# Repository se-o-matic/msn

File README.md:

# MSN

## MySensors Nodes
Hardware and software for MySensors.org IOT network.

The MSN PCB can be used for different node types. The minimal assembly consists of a Mega328P microcontroller (as seen on many Arduinos), a RFM69CW rf module with 868 or 433 MHz and some little stuff for reverse protection and battery monitoring.

With different assembly options, this PCB can be used for:
  * Temperature, humidity and pressure measurements (With BME280 assembled)
  * Sensor above with additional light level (with extra BH1750 on the proto field)
  * Cheap temperature measurement (With DS18B20 assembled on the small proto field)
  * IR-reader for digital Power meter (with external IR Head connected to UART)
  * Prototyping on Breadboards with soldered pin header

The PCB features also
  * ISP pins are connected to the pin header for flashing the bootloader
  * Arduino pro mini compatible pin header for connecting a UART-board
  * Optional LED for example for active transmission
  * Mounting holes for fitting in the “Strapubox 6090” case
  * A snap off proto board, which fit under or on top of the MSN PCB.

## V0.1
Software tested on breadboards. Hardware not tested, because the boards are still in production.

## V1.0
TBD Software modified to run on MSN PCB. Different improvements, like other libraries for enable power savings of the sensors.

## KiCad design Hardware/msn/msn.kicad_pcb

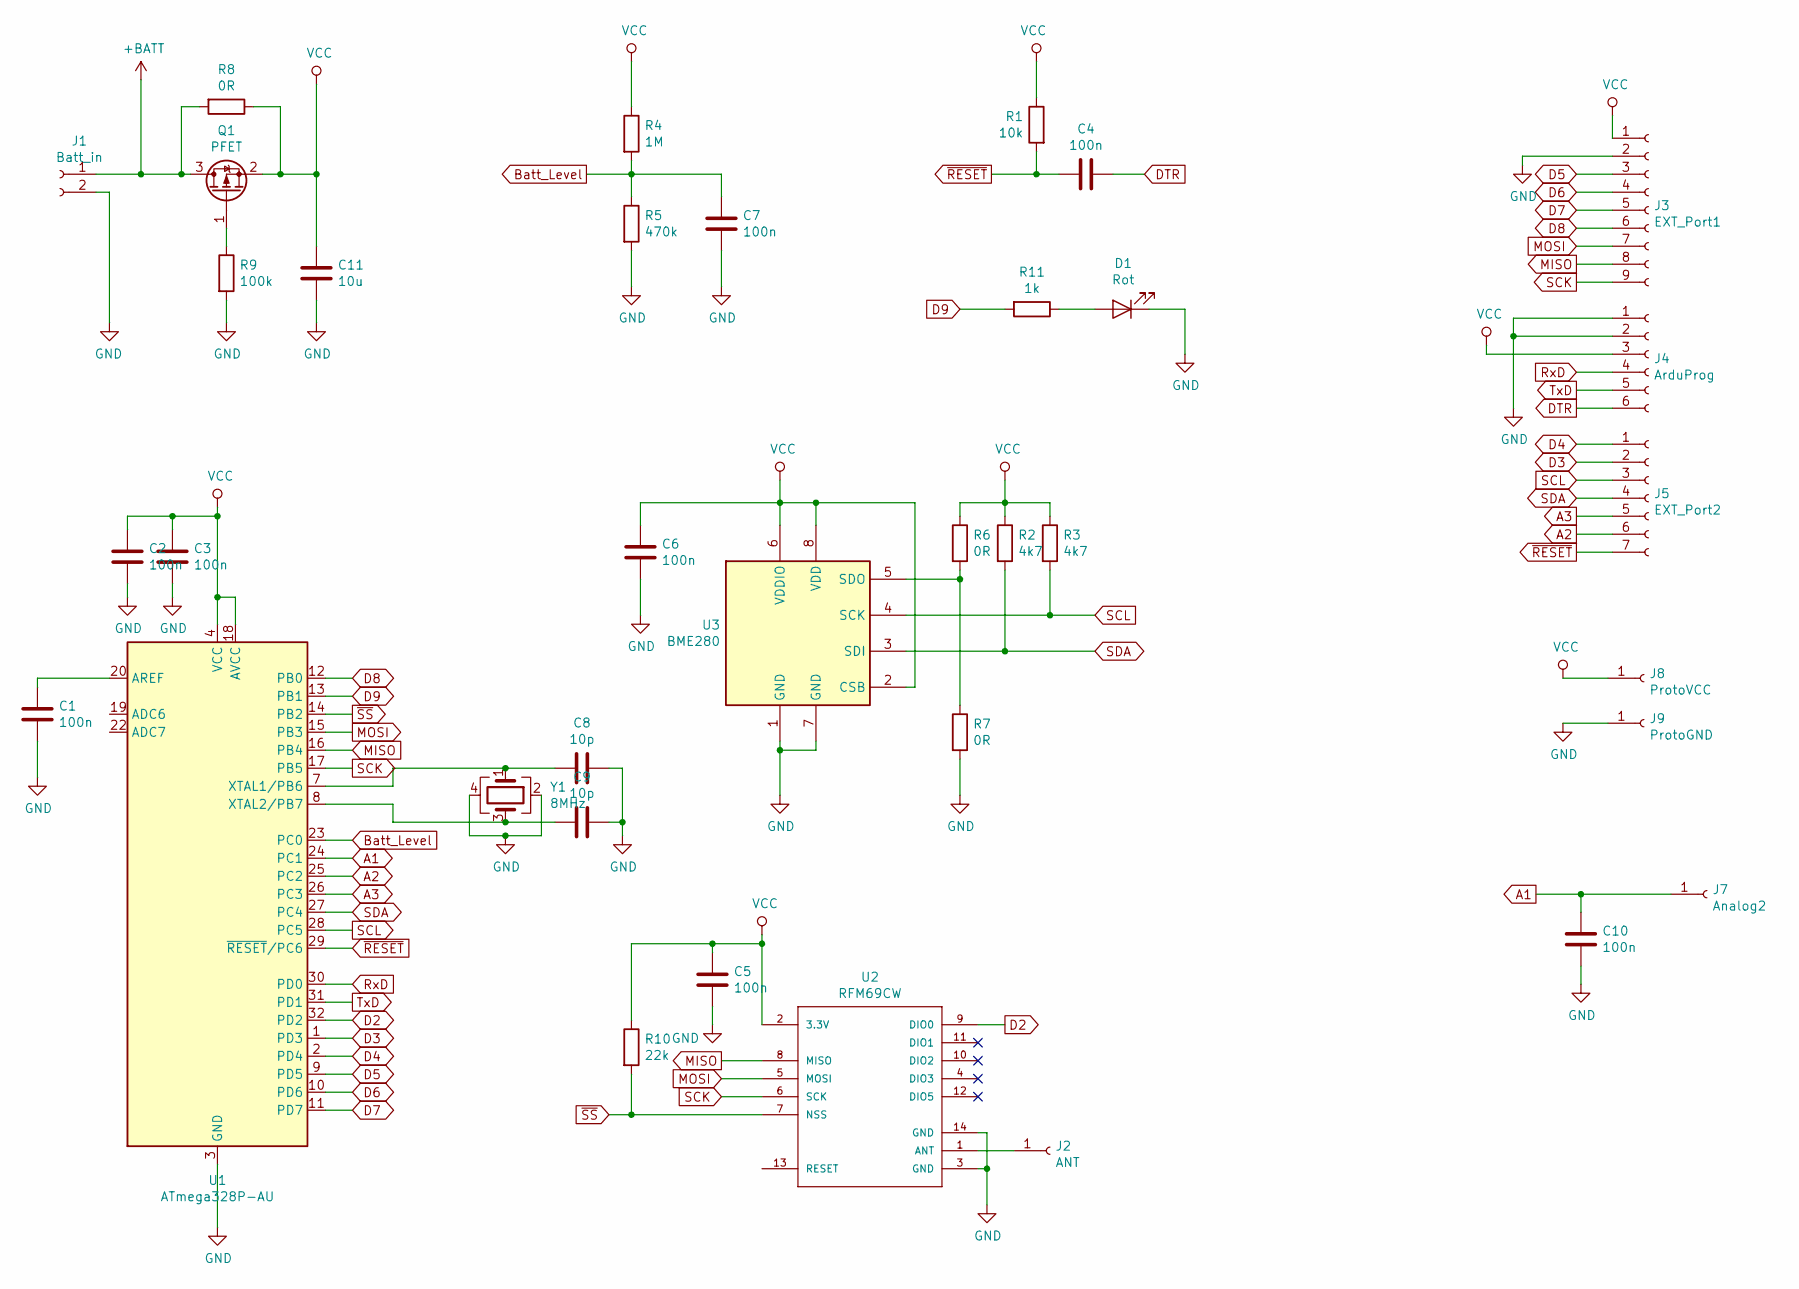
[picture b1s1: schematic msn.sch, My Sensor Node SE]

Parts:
C1, C2, C3, C4, C5, C6, C7, C10: 100n; C_0805_2012Metric
C8, C9: 10p; C_0805_2012Metric
C11: 10u; C_1210_3225Metric
D1: Rot; LED_0805_2012Metric
J1: Batt_in; Pin_Header_Straight_1x02_Pitch2.54mm
J2: ANT; Pin_Header_Straight_1x01_Pitch2.54mm
J3: EXT_Port1; PinHeader_1x09_P2.54mm_Vertical
J4: ArduProg; PinHeader_1x06_P2.54mm_Vertical
J5: EXT_Port2; PinHeader_1x07_P2.54mm_Vertical
J7: Analog2; PinHeader_1x01_P2.54mm_Vertical
J8: ProtoVCC; PinHeader_1x01_P2.54mm_Vertical
J9: ProtoGND; PinHeader_1x01_P2.54mm_Vertical
Q1: PFET; SOT-23
R1: 10k; R_0805_2012Metric
R2, R3: 4k7; R_0805_2012Metric
R4: 1M; R_0805_2012Metric
R5: 470k; R_0805_2012Metric
R6, R7, R8: 0R; R_0805_2012Metric
R9: 100k; R_0805_2012Metric
R10: 22k; R_0805_2012Metric
R11: 1k; R_0805_2012Metric
U1: ATmega328P-AU; LQFP-32_7x7mm_P0.8mm
U2: RFM69CW; RFM69CW-XXXS2
U3: BME280; Bosch_LGA-8_2.5x2.5mm_P0.65mm_ClockwisePinNumbering
Y1: 8MHz; Crystal_SMD_EuroQuartz_MQ-4pin_7.0x5.0mm

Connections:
+BATT: J1.1, Q1.3 (D), R8.2
A1: C10.1, J7.1, U1.24 (PC1)
A2: J5.6, U1.25 (PC2)
A3: J5.5, U1.26 (PC3)
Batt_Level: C7.1, R4.2, R5.1, U1.23 (PC0)
D2: U1.32 (PD2), U2.9 (DIO0)
D3: J5.2, U1.1 (PD3)
D4: J5.1, U1.2 (PD4)
D5: J3.3, U1.9 (PD5)
D6: J3.4, U1.10 (PD6)
D7: J3.5, U1.11 (PD7)
D8: J3.6, U1.12 (PB0)
D9: R11.2, U1.13 (PB1)
DTR: C4.2, J4.6
GND: C1.2, C2.2, C3.2, C5.2, C6.2, C7.2, C8.1, C9.1, C10.2, C11.2, D1.1 (K), J1.2, J3.2, J4.1, J4.2, J9.1, R5.2, R7.2, R9.2, U1.3 (GND), U1.5 (GND), U1.21 (GND), U2.3 (GND), U2.14 (GND), U3.1 (GND), U3.7 (GND), Y1.2, Y1.4
MISO: J3.8, U1.16 (PB4), U2.8 (MISO)
MOSI: J3.7, U1.15 (PB3), U2.5 (MOSI)
unnamed: C1.1, U1.20 (AREF)
unnamed: C8.2, U1.7 (XTAL1/PB6), Y1.1
unnamed: C9.2, U1.8 (XTAL2/PB7), Y1.3
unnamed: D1.2 (A), R11.1
unnamed: J2.1, U2.1 (ANT)
unnamed: Q1.1 (G), R9.1
unnamed: R6.2, R7.1, U3.5 (SDO)
RxD: J4.4, U1.30 (PD0)
SCK: J3.9, U1.17 (PB5), U2.6 (SCK)
SCL: J5.3, R3.2, U1.28 (PC5), U3.4 (SCK)
SDA: J5.4, R2.2, U1.27 (PC4), U3.3 (SDI)
TxD: J4.5, U1.31 (PD1)
VCC: C2.1, C3.1, C5.1, C6.1, C11.1, J3.1, J4.3, J8.1, Q1.2 (S), R1.1, R2.1, R3.1, R4.1, R6.1, R8.1, R10.1, U1.4 (VCC), U1.6 (VCC), U1.18 (AVCC), U2.2 (3.3V), U3.2 (CSB), U3.6 (VDDIO), U3.8 (VDD)
~RESET: C4.1, J5.7, R1.2, U1.29 (~RESET~/PC6)
~SS: R10.2, U1.14 (PB2), U2.7 (NSS)

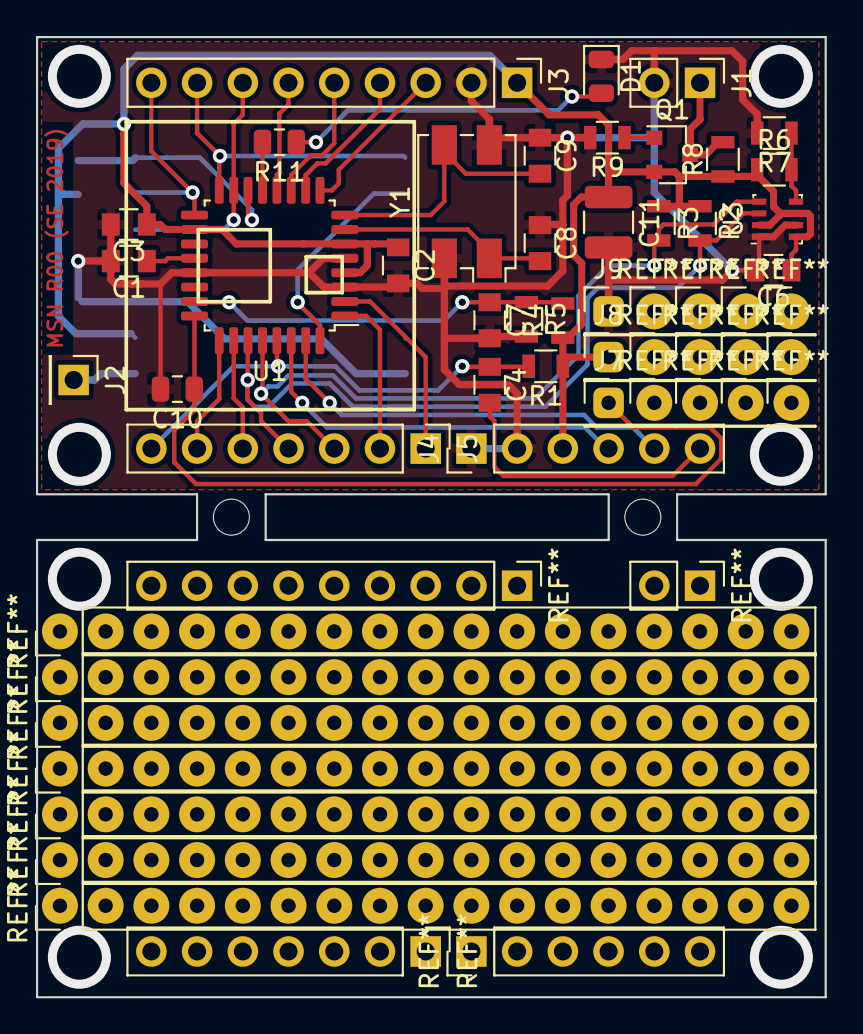
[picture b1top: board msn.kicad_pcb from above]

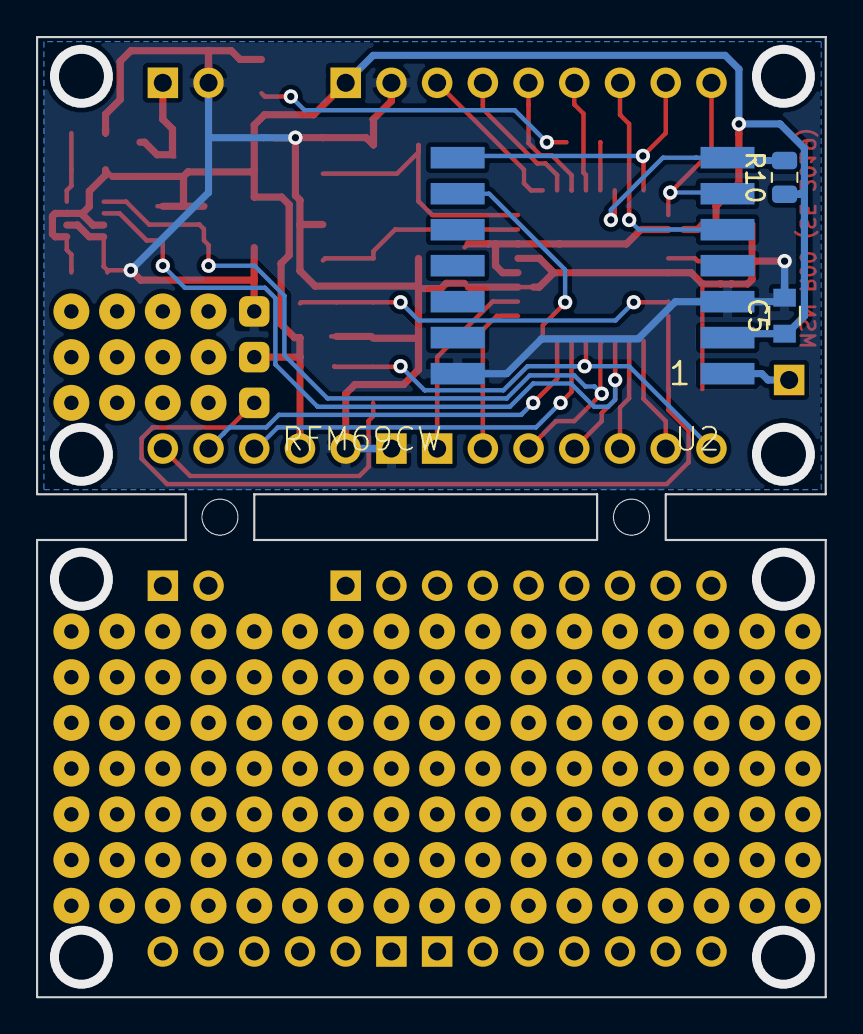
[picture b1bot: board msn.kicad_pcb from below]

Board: 2 copper layers, 43.8 x 53.3 mm, 36 parts (3 on the bottom side), 32 nets.

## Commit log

2019-10-09 Initial commit. Runs on breadboard.
2019-10-09 Added PDF printouts
2019-10-09 Added description
2019-10-22 Add license
2019-10-22 Added VS Code project files
2019-10-29 change library for BME280. The new one features the forced mode for energy saving.
2019-10-29 Added project files for VS Code
2019-10-29 Added code for outdoor node with BME280 and BH1750
2019-12-09 Changes for running on msn pcb
2019-12-09 Some optimizations
2019-12-09 Added project description
2019-12-09 Changed version string
